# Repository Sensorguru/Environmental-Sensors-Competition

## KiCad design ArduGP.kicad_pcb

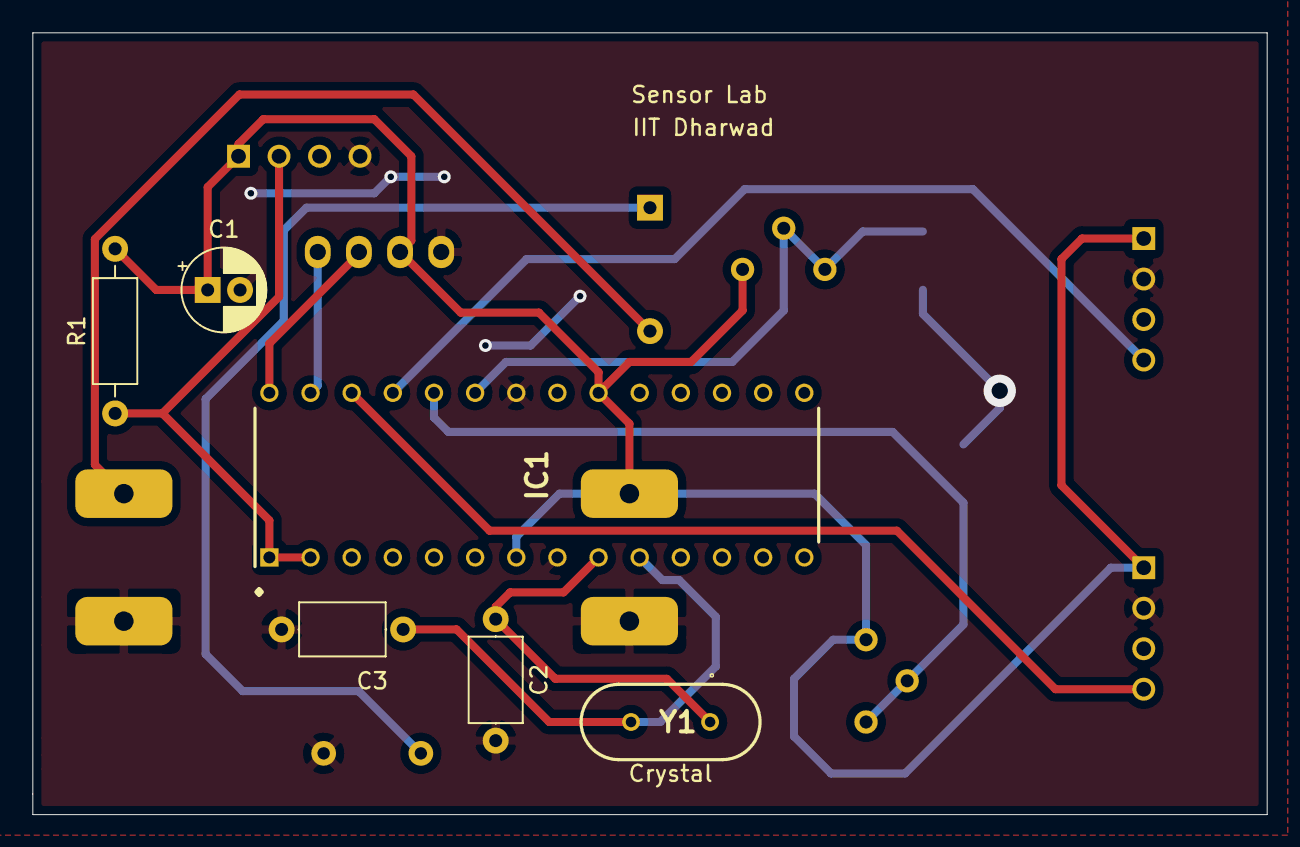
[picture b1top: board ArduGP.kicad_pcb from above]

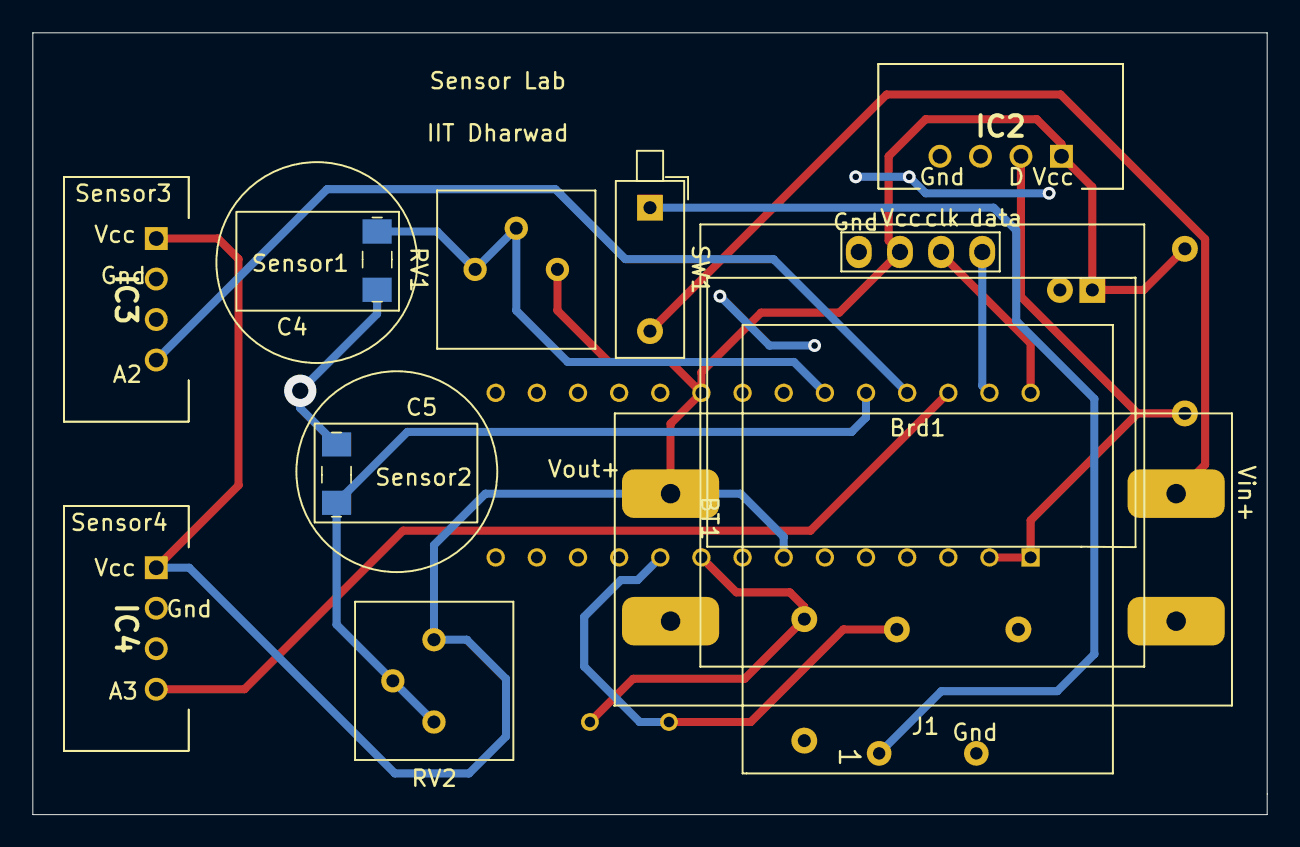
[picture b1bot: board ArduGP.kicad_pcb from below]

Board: 2 copper layers, 76.2 x 48.3 mm, 17 parts (11 on the bottom side), 13 nets.

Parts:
BT1: Battery_Cell; Lipo_3V7_450mAh
Brd1: SSD1306; 128x64OLED
C1: CP; CP_Radial_D5.0mm_P2.00mm
C2, C3: C; C_Axial_L5.1mm_D3.1mm_P7.50mm_Horizontal
C4: Sensor1; IDE_1x0p5
C5: Sensor2; IDE_1x0p5
IC1: ATMEGA328-PU; DIP1016W53P254L3468H457Q28N
IC2: DHT22
IC3: Sensor3; DHT22
IC4: Sensor4; DHT22
J1: Power Block; IVR_MT3608_stepup_powermodule
R1: R_US; R_Axial_DIN0207_L6.3mm_D2.5mm_P10.16mm_Horizontal
RV1, RV2: R_POT; Potentiometer_Bourns_3386P_Vertical
SW1: SW_DIP_x01; SW_DIP_SPSTx01_Piano_10.8x4.1mm_W7.62mm_P2.54mm
Y1: Crystal; HC49

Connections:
GND: BT1.2, Brd1.1, C1.2, C2.2, C3.2, C4.2, C5.2, IC1.8, IC1.22, IC2.4, IC3.2, IC4.2, J1.2, J1.3
unnamed: BT1.1, SW1.1
unnamed: Brd1.2, C1.1, IC1.7, IC1.20, IC2.1, IC3.1, IC4.1, J1.4, R1.2, RV1.1, RV2.1
unnamed: Brd1.3, IC1.28
unnamed: Brd1.4, IC1.27
unnamed: C2.1, IC1.9, Y1.1
unnamed: C3.1, IC1.10, Y1.2
unnamed: C4.1, IC1.23, RV1.2, RV1.3
unnamed: C5.1, IC1.24, RV2.2, RV2.3
unnamed: IC1.1, IC1.2, IC2.2, R1.1
unnamed: IC1.25, IC3.4
unnamed: IC1.26, IC4.4
unnamed: J1.1, SW1.2

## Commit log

2022-11-18 Create Arduino Code
